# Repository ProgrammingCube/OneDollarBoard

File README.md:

# One Dollar Board

## What is it?
This ATtiny85 board is a bit different than most. In fact, it is a spiritual successor to the [One Dollar Board](https://www.indiegogo.com/projects/one-dollar-board--5/x/14830965#/updates/all) Indiegogo project from 2016. This campaign made more than its goal and failed to deliver. Now, I am much more experienced than I was then. This project is my attempt to bring its idea to fruition.

While I have no where the buisness connections to create a true $1 board, this kit is something you can [buy]() or print yourself!

## Build process

This video will help you through the build process of the board. If you wish to have a writeup, [this]() is a link to the build how-to PDF. Those who purchase this kit will have also have a physical manual.

## Arduino IDE Setup
[Download Arduino IDE](https://www.arduino.cc/en/software)

In order to use this board seamlessly with the Arduino IDE, you need to install the Digispark Boards. These boards seem to be discontinued, but the json file is still extant.

Simply go to `File >> Preferencess` and click on the `Additional Boards Manager URLs` to add this entry:

`https://raw.githubusercontent.com/digistump/arduino-boards-index/master/package_digistump_index.json`

Click on OK.

Then, go `Tools >> Board... >> Boards Manager`. From here, search `Digistump`. Install the Digistump AVR Boards package. Accept any driver installs, we need these to talk to the boards because we are using a special bootloader.

#### Special note on the Bootloader***
Your ATtiny85 comes with a bootloader preinstalled, the [Micronucleus](https://github.com/SpenceKonde/ATTinyCore/blob/v2.0.0-devThis-is-the-head-submit-PRs-against-this/avr/extras/Ref_Micronucleus.md) bootloader. This allows one to program the chip via USB instead of using a middle-man ISP. You can still use an ISP if you want though, and its easy enough to flash back to the Micronucleus bootloader.

Here is the [link](https://github.com/ashishchoudhary9998/ATtiny85-Boot-loader) for the Micronucleus bootloader I have used. You can use a different one if you want, or if you're good enough, you can [make your own](https://ww1.microchip.com/downloads/aemDocuments/documents/MCU08/ApplicationNotes/ApplicationNotes/Basic-Bootloader-for-AVR-MCU-DA-Family-DS00003341C.pdf) or even [write it in C](https://github.com/m3y54m/simple-avr-bootloader) !

Once you have the board installed, select the correct board by doing `Tools >> Boards... >> Digistump AVR Boards >> Digispark (Default, 16.5mhz)`. Then select `Tools >> Programmer >> Micronucleus`.
**IF YOU CAN'T UPLOAD CODE AND YOU GET A MESSAGE WITH ONLY 60% UPLOADED, CHECK YOUR PROGRAMMER SELECTION** For some reason, Arduino IDE likes to deselect this.

## Microchip Studio Setup
[Download Microchip Studio](https://www.microchip.com/en-us/tools-resources/develop/microchip-studio#Downloads)

Setup is a bit more nuanced, and it can be a bit more difficult if your computer setup is different. However, the setup is almost the same!

Refer to the **Arduino IDE Setup** section and follow the guide to install the board in the Boards Manager. From there, we pick up.

To start a new project, you need to select what language you will use. From there, you need to add an `External Tool`.

`External Tools` is a fantastic feature in which you can run user-arbitrary executables with whatever command line options you want. Most uses exercise this feature to add custom binary upload programs to the IDE, making a seamless environment from code, compile, to upload.

Here's what to do. Go to `Tools >> External Tools...`. From there, click `Add`. Name the tool something meaningful, like `ATtiny85_VUSB` or `ATtiny85_Micronucleus` or something like that.

Next, we will fill out the `Command` field. This will specify which .exe to run when the External Tool is selected. For us, we need to use the `launcher.exe` supplied by the Arduino board install.

In order to find this tool, go to the Arduino IDE, go to `File >> Preferences` and enable `Show verbose output during` for `upload`. Then, select the Digistump board as in the **Arduino IDE Setup**, and build/upload a blank sketch to your ATtiny85 board.

In the `Output` window, you should see something like this:

`C:\Users\yourusername\AppData\Local\Arduino15\packages\digistump\tools\micronucleus\2.0a4/launcher.exe`

or wherever you have installed Arduino IDE. Copy this text to the `Command` field in the `External Tools...` window.

Next, you can copy this text directly to the `Arguments` field:

`-cdigispark --timeout 60 -Uflash:w:"$(TargetName)\$(TargetName)\Debug\$(TargetName).hex":i`

The variables `$(TargetNamee)` are used so the default .hex file will be uploaded, regardless of what the source file is named.

Next, we need to change the `Initial Directory` field. This directory will be the `Atmel Studio/7.0` folder's location like this:

`C:\Users\yourusername\Documents\Atmel Studio\7.0`

There's a strange bug in Microchip Studio in which spaces in the directory aren't handled right, so we'll do this to avoid problems.

Perfect! Now, when you use Microchip Studio, you can press `F7` to compile/assemble your program, then use `Tools >> your-external-tool` to upload! If you're good, you can [keybind your tool](https://onlinedocs.microchip.com/pr/GUID-ECD8A826-B1DA-44FC-BE0B-5A53418A47BD-en-US-12/index.html?GUID-A8EAD702-6D06-4931-9F49-AFE189F48A73)!
# FAQ
### The PWR LED doesn’t turn on!!!
- Check to make sure the power LED is installed the right way round. The molded flat plastic should be facing USER RIGHT.
- Double-check your USB connector solder joints. This LED is a direct power to ground connection, so if this doesn’t turn on, something simple is wrong.
- If your computer pops a message saying Overcurrent Detection, you may have a short in the upper-left quadrant of your board, or a short on the ATtiny85 IC socket. Ensure that all solder joints are isolated.
### The PB0 LED doesn’t blink!!!1!
Unfortunately, there can be many causes for this problem.
- Check if the LEDs are installed the right way round. The molded flat plastic should be facing USER RIGHT.
- Be sure that the ATtiny85 is installed correctly. Its index notch should be facing USER LEFT. Also, make sure its pins aren’t bent or sticking out from the socket.
- Double-check your soldering of the ATtiny85 IC socket. You wouldn’t believe how many times veteran hobbyists forget to solder entire chips!
### When I start using the other chips, nothing works!
- Check to see if there are shorts on the IC sockets.
- Check if the LD117V33 regulator is installed correctly. Refer to the images.
- Be careful on where you plug power and data cables. By design, this board is EXTREMELY flexible. I have tried to do my best to make the silkscreen clear, but it is still possible to accidentally switch around power and data pins. Refer to the pinout diagrams.

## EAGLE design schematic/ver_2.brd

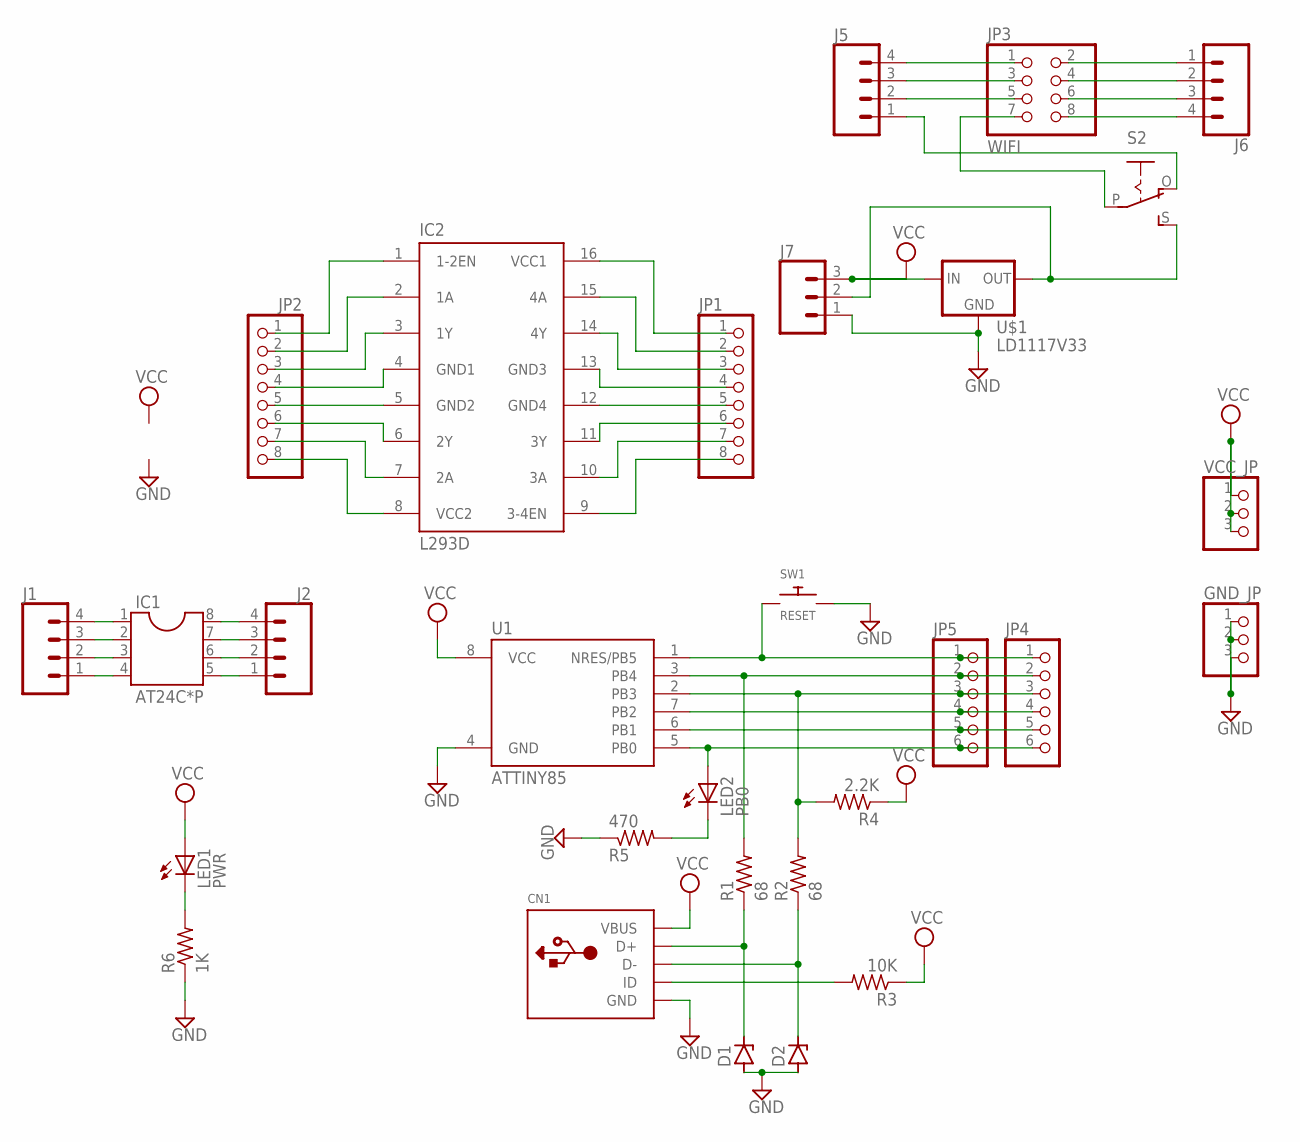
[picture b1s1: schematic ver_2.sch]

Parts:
CN1: USBTHM; USB-MINIB-THM
D1, D2: ZENER-DIODEDO34-7; DO34Z7
GND_JP: PINHD-1X3; 1X03
IC1: AT24C*P; SOCKET-08
IC2: L293D; DIL16
J1, J2: CONN_041X04_NO_SILK; 1X04_NO_SILK
J5, J6: CONN_04PTH; 1X04
J7: CONN_03; 1X03
JP1, JP2: PINHD-1X8CLEANBIG; 1X08-CLEANBIG
JP3: WIFI; 2X04
JP4, JP5: PINHD-1X6; 1X06
LED1: PWR; LED3MM
LED2: PB0; LED3MM
R1, R2: 68; 0204V
R3: 10K; 0204V
R4: 2.2K; 0204V
R5: 470; 0204V
R6: 1K; 0204V
S2: EG1218S; EG1218
SW1: RESET; TACT_PANA-EVQ
U1: ATTINY85; PDIP08_300MIL
U$1: LD1117V33
VCC_JP: PINHD-1X3; 1X03

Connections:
GND: CN1.GND, D1.A, D2.A, GND_JP.1, GND_JP.2, GND_JP.3, J7.1, R5.1, R6.1, SW1.P$2, U1.4 (GND), U$1.GND
unnamed: JP4.1, JP5.1, SW1.P$1, U1.1 (NRES/PB5)
unnamed: JP4.2, JP5.2, R1.2, U1.3 (PB4)
unnamed: JP4.3, JP5.3, R2.2, R4.2, U1.2 (PB3)
unnamed: JP4.4, JP5.4, U1.7 (PB2)
unnamed: JP4.5, JP5.5, U1.6 (PB1)
unnamed: JP4.6, JP5.6, LED2.A, U1.5 (PB0)
unnamed: IC1.4, J1.1
unnamed: IC1.3, J1.2
unnamed: IC1.2, J1.3
unnamed: IC1.1, J1.4
unnamed: IC1.5, J2.1
unnamed: IC1.6, J2.2
unnamed: IC1.7, J2.3
unnamed: IC1.8, J2.4
unnamed: CN1.ID, R3.2
unnamed: IC2.4 (GND1), JP2.4
unnamed: CN1.D+, D1.C, R1.1
unnamed: CN1.D-, D2.C, R2.1
unnamed: IC2.5 (GND2), JP2.5
unnamed: IC2.6 (2Y), JP2.6
unnamed: IC2.7 (2A), JP2.7
unnamed: IC2.8 (VCC2), JP2.8
unnamed: IC2.3 (1Y), JP2.3
unnamed: IC2.2 (1A), JP2.2
unnamed: IC2.1 (1-2EN), JP2.1
unnamed: J6.3, JP3.6
unnamed: J6.2, JP3.4
unnamed: JP3.7, S2.P
unnamed: J5.2, JP3.5
unnamed: J5.3, JP3.3
unnamed: J5.4, JP3.1
unnamed: J6.4, JP3.8
unnamed: J7.2, S2.S, U$1.OUT
unnamed: J6.1, JP3.2
unnamed: IC2.12 (GND4), JP1.5
unnamed: IC2.11 (3Y), JP1.6
unnamed: IC2.10 (3A), JP1.7
unnamed: IC2.9 (3-4EN), JP1.8
unnamed: IC2.13 (GND3), JP1.4
unnamed: IC2.14 (4Y), JP1.3
unnamed: IC2.15 (4A), JP1.2
unnamed: IC2.16 (VCC1), JP1.1
unnamed: LED2.K (C), R5.2
unnamed: LED1.K (C), R6.2
unnamed: J5.1, S2.O
VCC: CN1.VBUS, J7.3, LED1.A, R3.1, R4.1, U1.8 (VCC), U$1.IN, VCC_JP.1, VCC_JP.2, VCC_JP.3

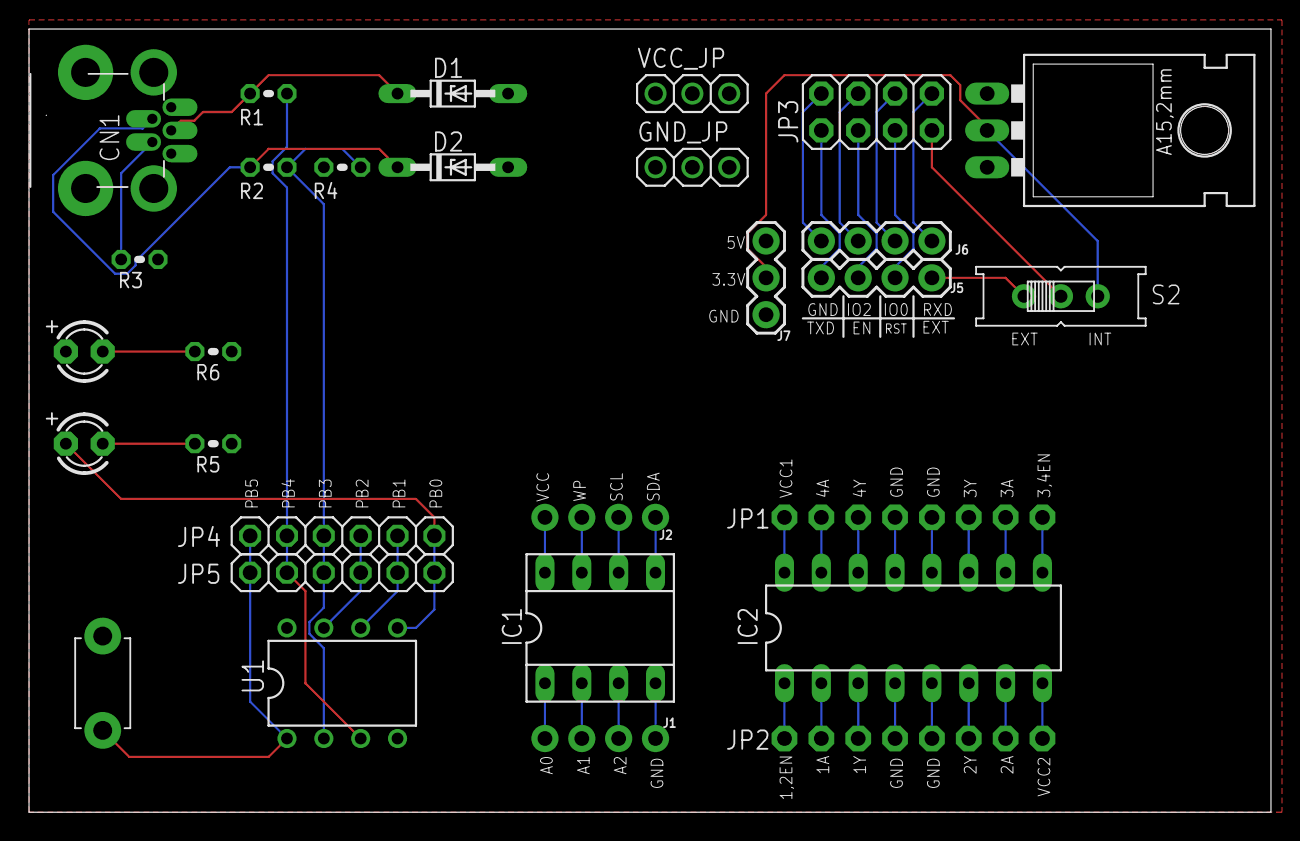
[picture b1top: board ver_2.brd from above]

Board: 2 copper layers, 85.6 x 54.0 mm, 29 parts (0 on the bottom side), 47 nets.

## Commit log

2024-08-18 first samples push
2024-08-18 schematic push
2024-08-19 readme update
2024-08-19 arduino EEPROM example update
2024-08-20 L293D code push
2024-08-20 samples doc fix
2024-08-21 readme faq update
2024-08-21 readme formatting update
2024-08-21 l293d c sample push
2024-08-21 c formatting fix
2024-08-21 naming standardization + at24c16d c example push
2024-08-21 readme links update
2024-08-24 manual push

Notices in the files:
parts and their libraries:
SparkFun-Connectors: Licensing: Creative Commons ShareAlike 4.0 International - https://creativecommons.org/licenses/by-sa/4.0
